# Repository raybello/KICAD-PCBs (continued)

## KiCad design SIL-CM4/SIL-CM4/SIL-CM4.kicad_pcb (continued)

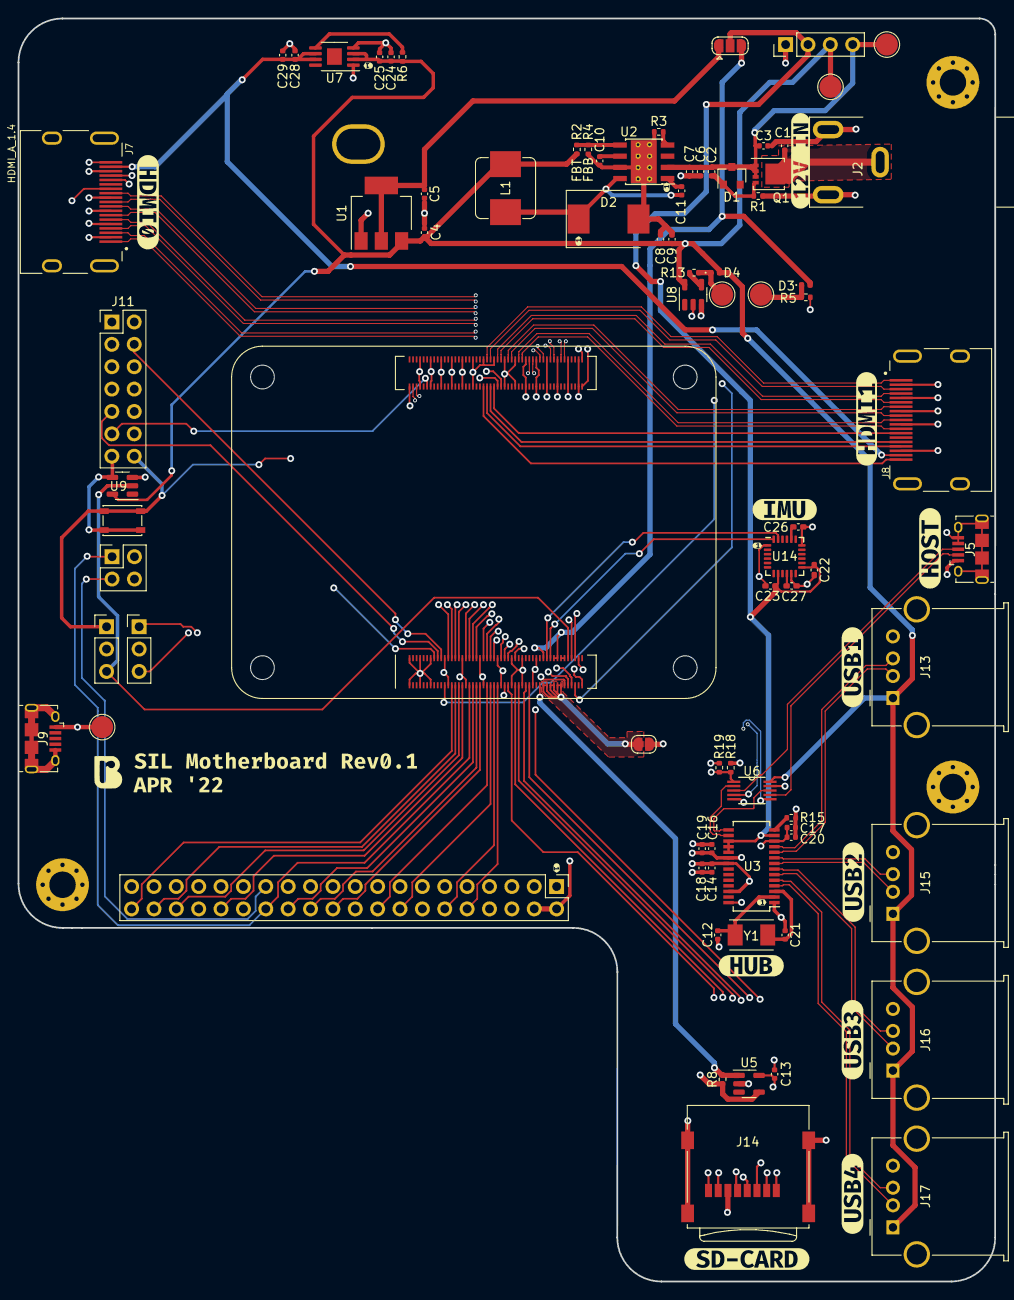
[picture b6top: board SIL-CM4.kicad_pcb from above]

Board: 4 copper layers, 110.9 x 143.4 mm, 103 parts (0 on the bottom side), 118 nets.

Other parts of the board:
kibuzzard-6252E1A6: G***; kibuzzard-6252E1A6
kibuzzard-6252E5F1: G***; kibuzzard-6252E5F1
kibuzzard-6252E6B2: G***; kibuzzard-6252E6B2
kibuzzard-6252E6F0: G***; kibuzzard-6252E6F0
kibuzzard-6252E7D0: G***; kibuzzard-6252E7D0
kibuzzard-6252E8F1, kibuzzard-6252E8F1#2, kibuzzard-6252E8F1#3, kibuzzard-6252E8F1#4, kibuzzard-6252E8F1#5, kibuzzard-6252E8F1#6: G***; kibuzzard-6252E8F1
kibuzzard-6252E20C: G***; kibuzzard-6252E20C
kibuzzard-6252E67C: G***; kibuzzard-6252E67C
kibuzzard-6252E74F: G***; kibuzzard-6252E74F
kibuzzard-6252E662: G***; kibuzzard-6252E662
kibuzzard-6252E708: G***; kibuzzard-6252E708
kibuzzard-6252E722: G***; kibuzzard-6252E722
kibuzzard-6252E763: G***; kibuzzard-6252E763
kibuzzard-6252E779: G***; kibuzzard-6252E779

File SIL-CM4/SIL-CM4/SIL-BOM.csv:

Comment,Designator,Footprint,LCSC
100nF,"C1,C2,C11",Capacitor_SMD:C_0402_1005Metric,C129131
C_SS 3nF,C10,Capacitor_SMD:C_0402_1005Metric,C2857967
22pF,"C12,C21",Capacitor_SMD:C_0402_1005Metric,C342943
10u,C13,Capacitor_SMD:C_0402_1005Metric,C315248
0.1uF,"C18,C19,C20,C25,C28",Capacitor_SMD:C_0402_1005Metric,C129131
10nF,C22,Capacitor_SMD:C_0402_1005Metric_Pad0.74x0.62mm_HandSolder,C60133
0.1uF,"C23,C27",Capacitor_SMD:C_0402_1005Metric_Pad0.74x0.62mm_HandSolder,C129131
2.2nF,C26,Capacitor_SMD:C_0402_1005Metric_Pad0.74x0.62mm_HandSolder,C1531
120uF,C29,Capacitor_SMD:C_0402_1005Metric,C445416
10uF,"C3,C4,C5,C14,C16,C17,C24",Capacitor_SMD:C_0402_1005Metric,C315248
2.2uF,"C6,C7",Capacitor_SMD:C_0402_1005Metric,C385887
47uF,"C8,C9",Capacitor_SMD:C_0402_1005Metric,C16780
MMBZ5242B,D1,Diode_SMD:D_SOT-23_ANK,C193729
B340AG,D2,Diode_SMD:D_SMC,C433997
LED_GREEN,D3,LED_SMD:LED_0402_1005Metric,C264408
LED_RED,D4,LED_SMD:LED_0402_1005Metric,C136765
MountingHole,"H1,H2,H3,H4",MountingHole:MountingHole_3mm_Pad_Via,null
Power Jumper,J1,Connector_PinHeader_2.54mm:PinHeader_1x04_P2.54mm_Vertical,null
PI_20,J10,Connector_PinHeader_2.54mm:PinHeader_2x20_P2.54mm_Vertical,null
ANALOG_BOOT_PINS ,J11,Connector_PinHeader_2.54mm:PinHeader_2x07_P2.54mm_Vertical,null
USB_A,"J13,J15,J16,J17",Connector_USB:USB_A_Molex_67643_Horizontal,C591765
Micro_SD_Card,J14,Connector_Card:microSD_HC_Wuerth_693072010801,Source for MCU
Barrel_Jack,J2,Connector_BarrelJack:BarrelJack_CUI_PJ-063AH_Horizontal_CircularHoles,C381112
WiFi_BT_Disable,J3,Connector_PinHeader_2.54mm:PinHeader_1x03_P2.54mm_Vertical,null
GLOBAL_EN_RUN_PG,J4,Connector_PinHeader_2.54mm:PinHeader_1x03_P2.54mm_Vertical,null
USB_B_Micro,"J5,J9",Connector_USB:USB_Micro-B_Amphenol_10118194_Horizontal,C132563
THD-02-R,J6,Connector_PinHeader_2.54mm:PinHeader_2x02_P2.54mm_Vertical,null
HDMI_A_1.4,"J7,J8",CM4IO:EDAC 690-019-298-412,C138388 
3v3_SEL,JP1,Jumper:SolderJumper-3_P1.3mm_Open_RoundedPad1.0x1.5mm,null
CPU_5V_EN,JP2,Jumper:SolderJumper-2_P1.3mm_Open_RoundedPad1.0x1.5mm,null
8.2uH,L1,Inductor_SMD:L_Bourns_SRP7028A_7.3x6.6mm,Mouser 652-SRP7028AA-8R2M
ComputeModule4-CM4,Module1,CM4IO:Raspberry-Pi-4-Compute-Module,null
DMP3013SFV,Q1,Package_SON:Diodes_PowerDI3333-8,C461072
12K,R1,Resistor_SMD:R_0402_1005Metric,C2909316
2.7K,R15,Resistor_SMD:R_0402_1005Metric,C160491
2.2K,"R18,R19",Resistor_SMD:R_0402_1005Metric,C2906865
100K,R2,Resistor_SMD:R_0402_1005Metric,C144809
49.9K,R3,Resistor_SMD:R_0402_1005Metric,C2906873
17.8K,R4,Resistor_SMD:R_0402_1005Metric,C77605
1K,"R5,R13",Resistor_SMD:R_0402_1005Metric,C226166
10K,R6,Resistor_SMD:R_0402_1005Metric,C258091
12K 1%,R8,Resistor_SMD:R_0402_1005Metric,C2909316
WAKE_BTN,SW1,Button_Switch_SMD:SW_SPST_PTS810,C116501
USB_5V_pad,TP1,TestPoint:TestPoint_Pad_D2.5mm,null
12V_pad,TP2,TestPoint:TestPoint_Pad_D2.5mm,null
Reg_5V_pad,TP3,TestPoint:TestPoint_Pad_D2.5mm,null
LED_FVoltage,TP4,TestPoint:TestPoint_Pad_D2.5mm,null
TestPoint,TP5,TestPoint:TestPoint_Pad_D2.5mm,null
LD1117S33TR_SOT223,U1,Package_TO_SOT_SMD:SOT-223-3_TabPin2,C347229
MPU-6050,U14,Sensor_Motion:InvenSense_QFN-24_4x4mm_P0.5mm,Source for MCU
LMR16030SDDAR,U2,Package_SO:Texas_HSOP-8-1EP_3.9x4.9mm_P1.27mm_ThermalVias,C136648
FE1.1s,U3,Package_SO:SSOP-28_3.9x9.9mm_P0.635mm, C9359
AP2822CKATR-G1,U5,Package_TO_SOT_SMD:SOT-23-5,Mouser 621-AP2822CKATR-G1
FSUSB30MUX,U6,Symbol:SOP50P490X110-10N,Mouser 512-FSUSB30MUX
AP2141D_(Active_Low),U7,Package_SO:MSOP-8-1EP_3x3mm_P0.65mm_EP1.68x1.88mm,Mouser 621-AP2141DMPG-13
74LVC1G07,"U8,U9",Package_TO_SOT_SMD:SOT-23-5,Mouser 595-74LVC1G07DBVTE4
12MHz,Y1,Crystal:Crystal_SMD_TXC_7A-2Pin_5x3.2mm,C557138

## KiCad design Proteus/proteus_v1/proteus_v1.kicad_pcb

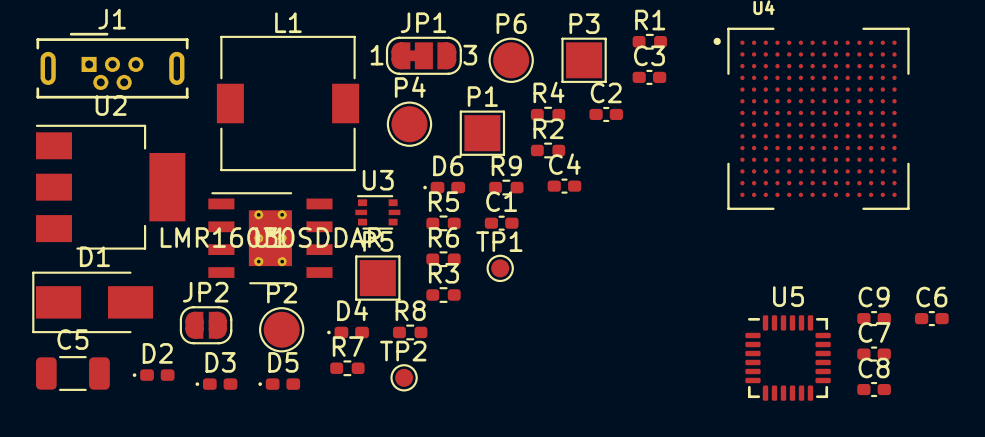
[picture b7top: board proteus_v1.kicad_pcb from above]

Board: 2 copper layers, 41 parts (0 on the bottom side), 28 nets, no tracks yet.

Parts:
C1: 4.7uF; C_0402_1005Metric_Pad0.74x0.62mm_HandSolder
C2, C4: 10uF; C_0402_1005Metric_Pad0.74x0.62mm_HandSolder
C3, C7, C9: 0.1uF; C_0402_1005Metric_Pad0.74x0.62mm_HandSolder
C5: 100uF; C_1206_3216Metric
C6: 2.2nF; C_0402_1005Metric_Pad0.74x0.62mm_HandSolder
C8: 10nF; C_0402_1005Metric_Pad0.74x0.62mm_HandSolder
D1: D_Schottky; D_SMA
D2: LED_B; LED_0402_1005Metric_Pad0.77x0.64mm_HandSolder
D3: LED_R; LED_0402_1005Metric_Pad0.77x0.64mm_HandSolder
D4, D5, D6: LED_G; LED_0402_1005Metric_Pad0.77x0.64mm_HandSolder
J1: Connector_USB_B_Micro; USB_Micro-B_Wuerth_614105150721_Vertical
JP1: SolderJumper_3_Bridged12; SolderJumper-3_P1.3mm_Bridged12_RoundedPad1.0x1.5mm_NumberL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
JP2: IO_EN; SolderJumper-2_P1.3mm_Open_RoundedPad1.0x1.5mm
L1: 8.2uH; L_7.3x7.3_H3.5
P1: LIPO_VCC; TestPoint_Pad_2.0x2.0mm
P2: LIPO_GND; TestPoint_Pad_D2.0mm
P3: ESC1_VCC; TestPoint_Pad_2.0x2.0mm
P4: ESC1_GND; TestPoint_Pad_D2.0mm
P5: ESC2_VCC; TestPoint_Pad_2.0x2.0mm
P6: ESC2_GND; TestPoint_Pad_D2.0mm
R1, R2: 49.9K; R_0402_1005Metric_Pad0.72x0.64mm_HandSolder
R3: 100K; R_0402_1005Metric_Pad0.72x0.64mm_HandSolder
R4: 17.8K; R_0402_1005Metric_Pad0.72x0.64mm_HandSolder
R5: 47R; R_0402_1005Metric_Pad0.72x0.64mm_HandSolder
R6, R7, R8, R9: 62R; R_0402_1005Metric_Pad0.72x0.64mm_HandSolder
TP1: GND_BAT_Probe; TestPoint_Pad_D1.0mm
TP2: 5V_BAT_Probe; TestPoint_Pad_D1.0mm
U1: LMR16030SDDAR
U2: LD1117S33TR_SOT223; SOT-223-3_TabPin2
U3: USBLC6-2P6; SOT-666
U4: MIMXRT1062DVL6A; BGA196C65P14X14_1000X1000X152N
U5: MPU-6050; InvenSense_QFN-24_4x4mm_P0.5mm

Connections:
3V3_IO: C8.2, C9.1, JP2.2 (B), U5.8 (VDDIO), U5.13 (VDD)
+3V3: C4.1, D5.2 (A), JP2.1 (A), U2.2 (VO)
+5V: C5.1, D6.2 (A), JP1.3 (B), L1.2, R2.2, R3.1
FC_USB_VBUS: J1.1 (VBUS), JP1.1 (A), U3.5 (VBUS)
GND: C1.2, C2.2, C4.2, C5.2, C6.2, C7.2, C8.1, C9.2, D1.2 (A), J1.5 (GND), J1.6 (Shield), P2.1 (PAD), P4.1 (PAD), P6.1 (PAD), R1.2, R4.2, R5.2, R6.2, R7.2, R8.2, R9.2, TP1.1, U1.7 (GND), U1.9 (PAD), U2.1 (GND), U3.2 (GND), U5.1 (CLKIN), U5.11 (FSYNC), U5.18 (GND)
unnamed: C3.1, U1.1 (BOOT)
unnamed: C3.2, D1.1 (K), L1.1, U1.8 (SW)
unnamed: C6.1, U5.20 (CPOUT)
unnamed: C7.1, U5.10 (REGOUT)
unnamed: D2.1 (K), R5.1
unnamed: D3.1 (K), R6.1
unnamed: D4.1 (K), R7.1
unnamed: D5.1 (K), R8.1
unnamed: D6.1 (K), R9.1
unnamed: J1.2 (D-), U3.4 (I/O2)
unnamed: J1.3 (D+), U3.6 (I/O1)
unnamed: R1.1, U1.4 (RT_SYNC)
unnamed: R2.1, U1.6 (PWRGD)
unnamed: R3.2, R4.1, U1.5 (FB)
unnamed: U4.A1 (VSS), U4.A14 (VSS), U4.B5 (VSS), U4.B10 (VSS), U4.E2 (VSS), U4.E13 (VSS), U4.G7 (VSS), U4.G8 (VSS), U4.H7 (VSS), U4.H8 (VSS), U4.J7 (VSS), U4.J8 (VSS), U4.K2 (VSS), U4.K13 (VSS), U4.L9 (VSS), U4.N5 (VSS), U4.N8 (VSS), U4.P1 (VSS), U4.P14 (VSS)
unnamed: U4.E6 (NVCC_EMC), U4.F5 (NVCC_EMC)
unnamed: U4.E9 (NVCC_GPIO), U4.F10 (NVCC_GPIO), U4.J10 (NVCC_GPIO)
unnamed: U4.F6 (VDD_SOC_IN), U4.F7 (VDD_SOC_IN), U4.F8 (VDD_SOC_IN), U4.F9 (VDD_SOC_IN), U4.G6 (VDD_SOC_IN), U4.G9 (VDD_SOC_IN), U4.H6 (VDD_SOC_IN), U4.H9 (VDD_SOC_IN), U4.J9 (VDD_SOC_IN)
unnamed: U4.L1 (DCDC_IN), U4.L2 (DCDC_IN)
unnamed: U4.M1 (DCDC_LP), U4.M2 (DCDC_LP)
unnamed: U4.N1 (DCDC_GND), U4.N2 (DCDC_GND)
REG_5VIN: C2.1, JP1.2 (C), U2.3 (VI)
VCC: C1.1, P1.1 (PAD), P3.1 (PAD), P5.1 (PAD), TP2.1, U1.2 (VIN)

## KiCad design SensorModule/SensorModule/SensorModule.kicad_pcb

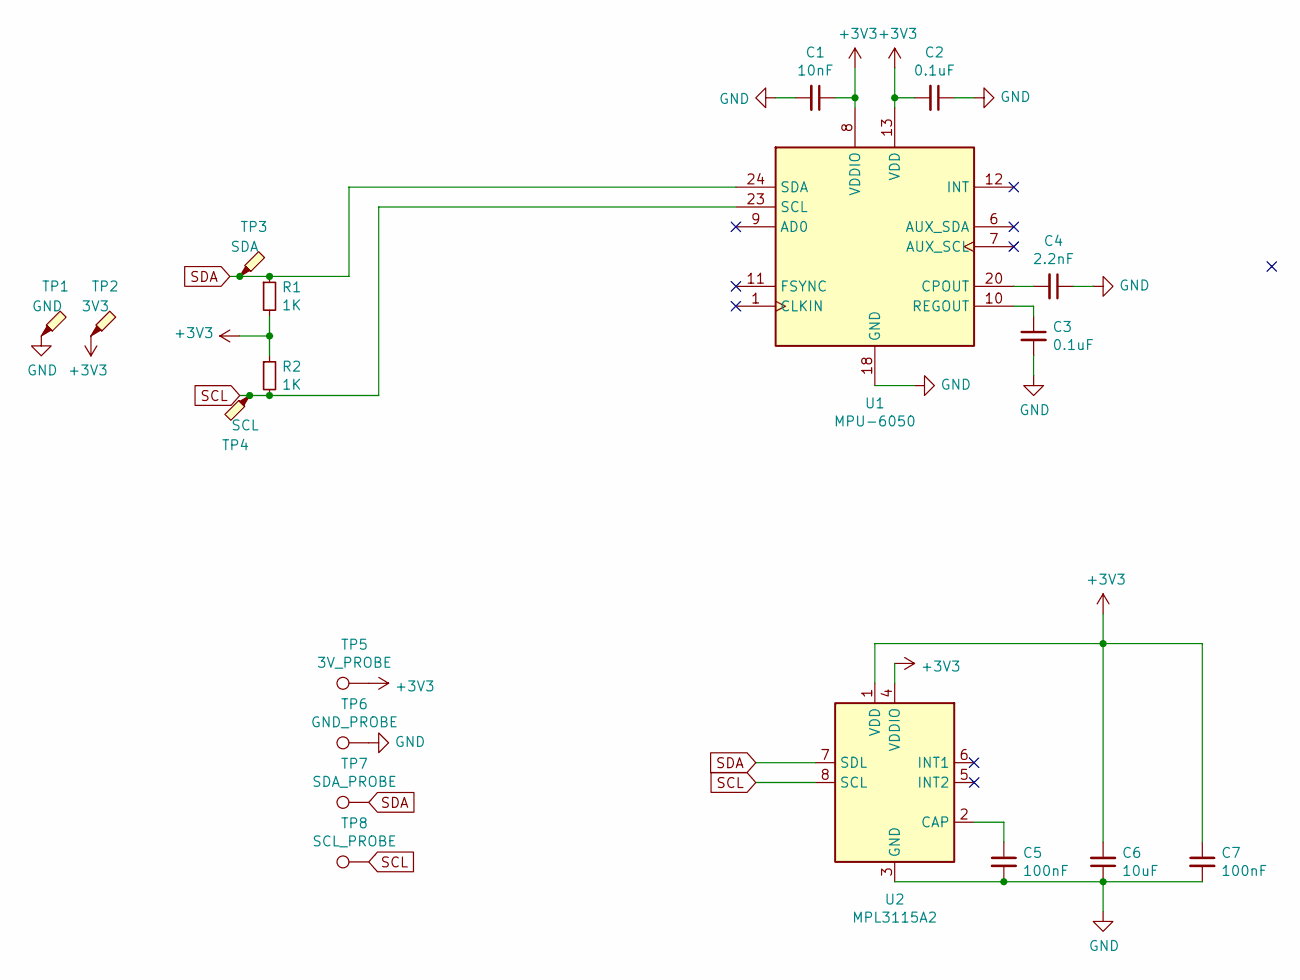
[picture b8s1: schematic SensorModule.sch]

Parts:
C1: 10nF; C_0402_1005Metric_Pad0.74x0.62mm_HandSolder
C2, C3: 0.1uF; C_0402_1005Metric_Pad0.74x0.62mm_HandSolder
C4: 2.2nF; C_0402_1005Metric_Pad0.74x0.62mm_HandSolder
C5, C7: 100nF; C_0402_1005Metric_Pad0.74x0.62mm_HandSolder
C6: 10uF; C_0402_1005Metric_Pad0.74x0.62mm_HandSolder
R1, R2: 1K; R_0402_1005Metric_Pad0.72x0.64mm_HandSolder
TP1: GND; TestPoint_Pad_4.0x4.0mm
TP2: 3V3; TestPoint_Pad_4.0x4.0mm
TP3: SDA; TestPoint_Pad_4.0x4.0mm
TP4: SCL; TestPoint_Pad_4.0x4.0mm
TP5: 3V_PROBE; TestPoint_Pad_D1.0mm
TP6: GND_PROBE; TestPoint_Pad_D1.0mm
TP7: SDA_PROBE; TestPoint_Pad_D1.0mm
TP8: SCL_PROBE; TestPoint_Pad_D1.0mm
U1: MPU-6050; InvenSense_QFN-24_4x4mm_P0.5mm
U2: MPL3115A2; NXP_LGA-8_3x5mm_P1.25mm_H1.1mm

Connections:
+3V3: C1.1, C2.2, C6.2, C7.1, R1.2, R2.1, TP2.1, TP5.1, U1.8 (VDDIO), U1.13 (VDD), U2.1 (VDD), U2.4 (VDDIO)
GND: C1.2, C2.1, C3.2, C4.1, C5.2, C6.1, C7.2, TP1.1, TP6.1, U1.18 (GND), U2.3 (GND)
unnamed: C3.1, U1.10 (REGOUT)
unnamed: C4.2, U1.20 (CPOUT)
unnamed: C5.1, U2.2 (CAP)
SCL: R2.2, TP4.1, TP8.1, U1.23 (SCL), U2.8 (SCL)
SDA: R1.1, TP3.1, TP7.1, U1.24 (SDA), U2.7 (SDL)

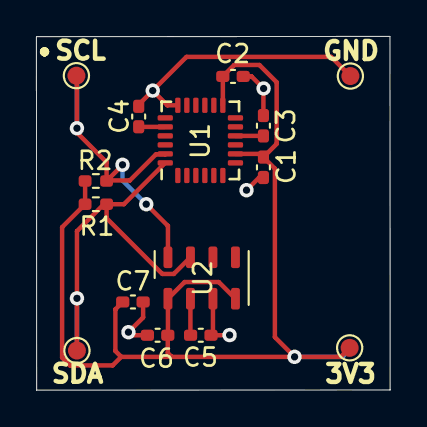
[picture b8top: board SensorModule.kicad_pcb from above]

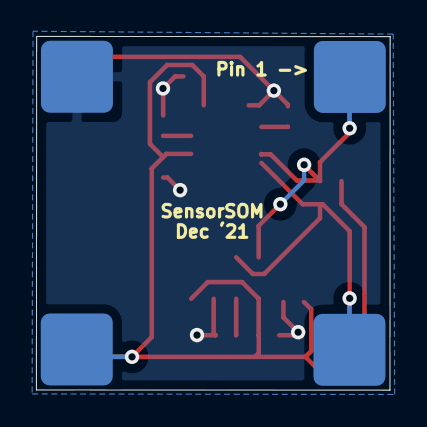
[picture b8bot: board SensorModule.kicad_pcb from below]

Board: 2 copper layers, 19.6 x 19.6 mm, 19 parts (4 on the bottom side), 7 nets.

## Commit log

2021-05-10 laptop sync
2021-05-10 update laptop
2021-05-12 PCB Bottom Complete
2021-05-19 added mpu6050
2021-05-20 Submitted PCB Design
2021-07-24 added hermes
2021-08-03 changed board to pi-zero HAT design
2021-08-04 routed rp2040
2021-08-05 added GND & 3V3 copper pours
2021-09-27 new designs
2021-09-28 Added OSHW and other tags
2022-01-26 added piUAV & Proteus_v1
2022-02-05 Added initial voltage circuit
2022-04-19 Added SIL-CM4
2022-04-19 Added SIL-BOM.csv
2022-04-19 Added xlsx BOM
2022-04-26 Added BOM tools
2022-05-29 New Linux boards added
2022-06-20 Hermes v2
2023-02-05 new stuff
2023-02-05 more new stuff
2024-08-12 added mac files
2025-07-24 Added VoltPak 1000
2025-07-24 New commit
2025-07-24 added backups
2025-07-24 esp32s3: added main components, need to add flash chip
2025-07-26 almost done mcu
2025-08-06 Adding volpak 1000
2025-08-09 more circuit stuff
2025-08-24 finished layout, yet to source parts
2025-09-04 completed layout
2025-09-05 generated plots
2026-06-03 voltpak ckt
